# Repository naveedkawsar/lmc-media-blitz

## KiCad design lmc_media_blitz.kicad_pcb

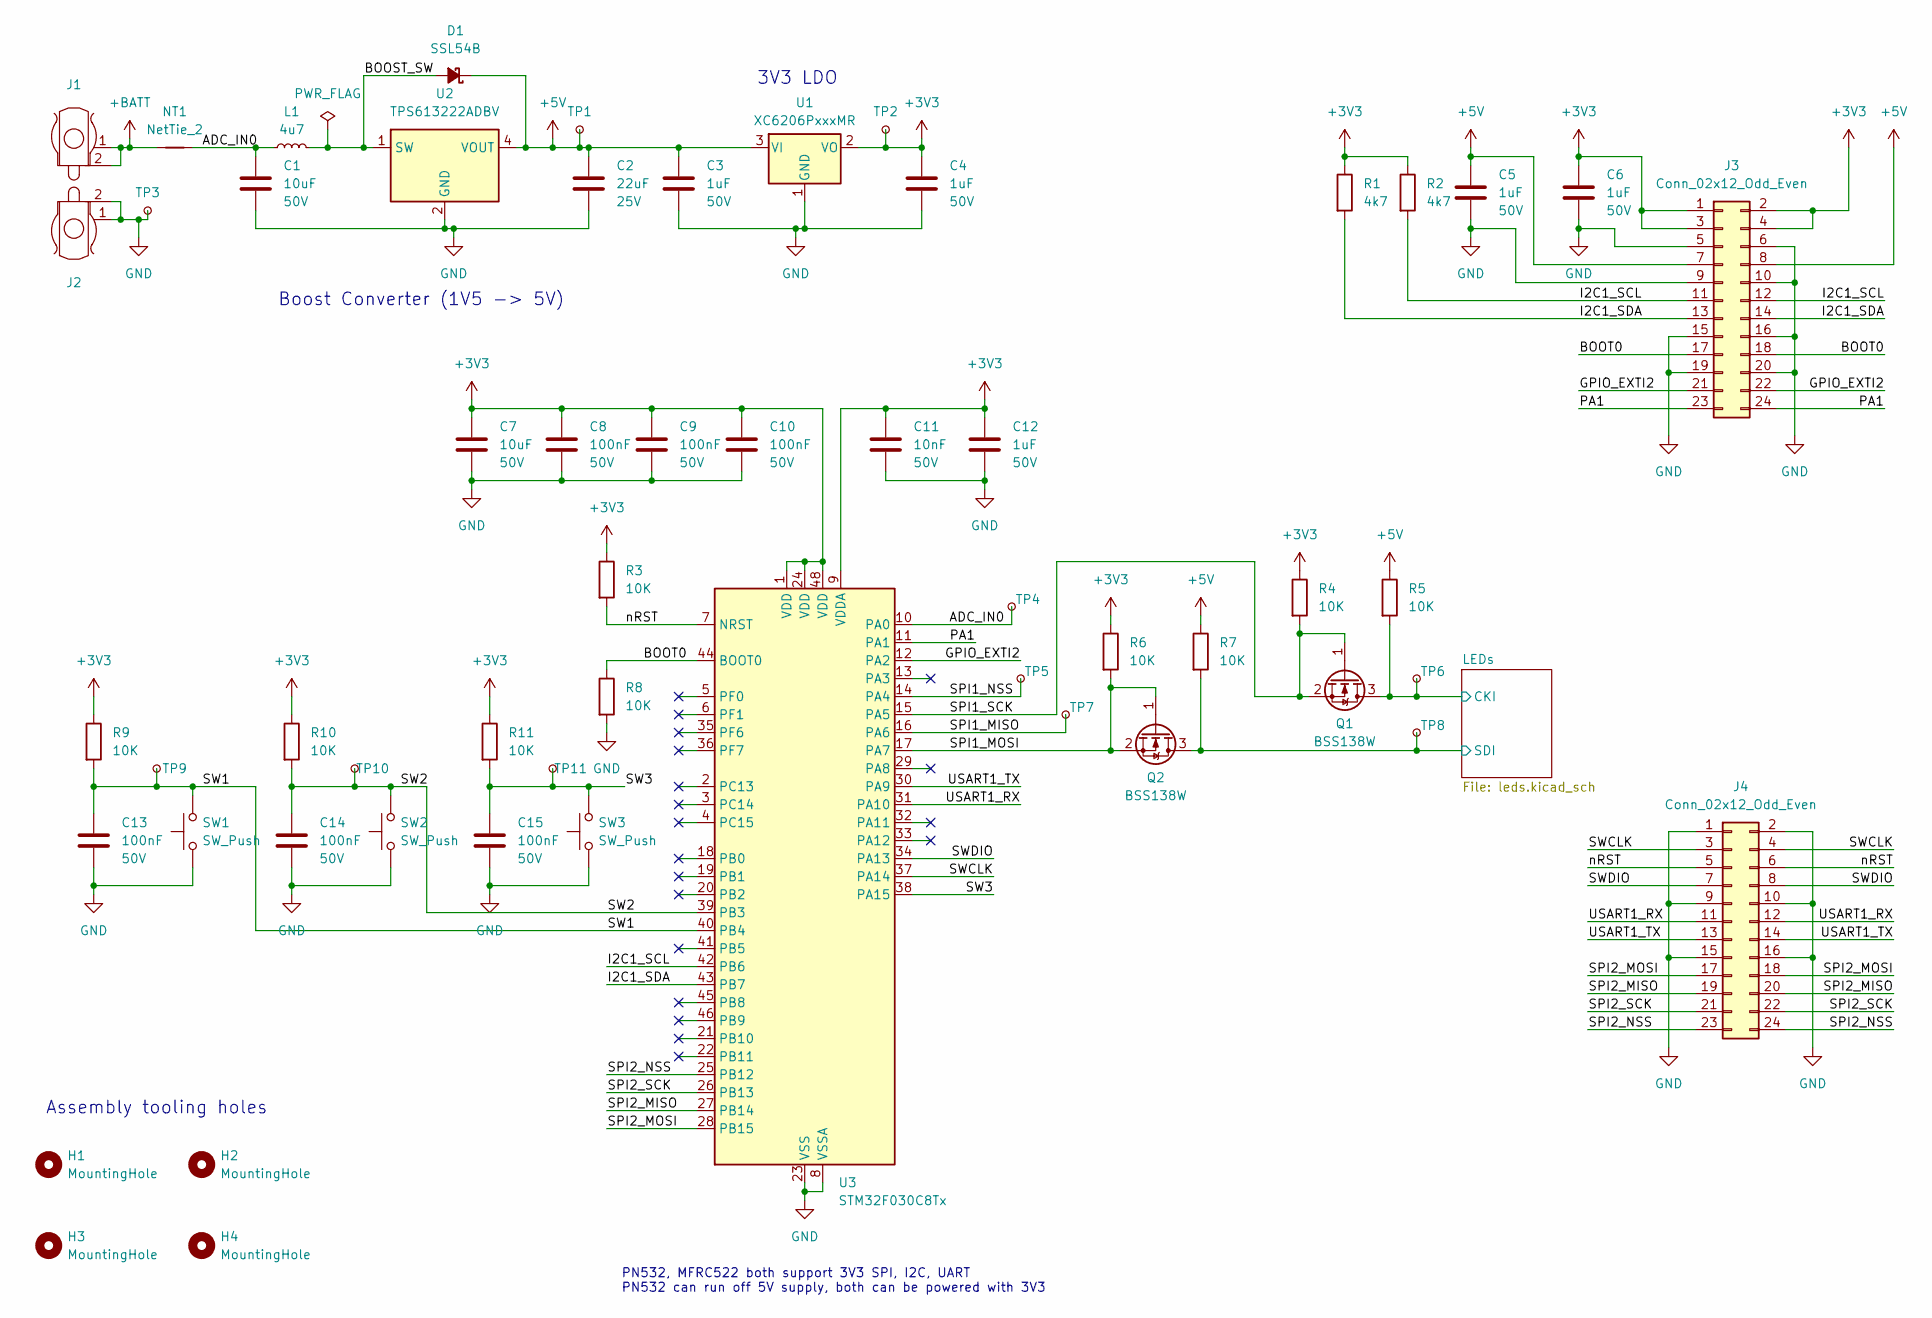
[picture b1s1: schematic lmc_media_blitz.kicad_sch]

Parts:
C1, C7: 10uF; C_0805_2012Metric; Voltage 50V; LCSC Part # C440198
C2: 22uF; C_0805_2012Metric; Voltage 25V; LCSC Part # C16780
C3, C4, C5, C6, C12: 1uF; C_0805_2012Metric; Voltage 50V; LCSC Part # C28323
C8, C9, C10, C13, C14, C15: 100nF; C_0603_1608Metric; Voltage 50V; LCSC Part # C14663
C11: 10nF; C_0603_1608Metric; Voltage 50V; LCSC Part # C57112
D1: SSL54B; D_SMB; LCSC Part # C28646278
H1, H2, H3, H4: MountingHole; JLCPCB_ToolingHole_45.4mils
J1, J2: Keystone82; LCSC Part # C964880
J3, J4: Conn_02x12_Odd_Even; PinHeader_2x12_P2.54mm_Vertical
L1: 4u7; L_Changjiang_FNR4030S; LCSC Part # C167874
NT1: NetTie_2; NetTie-2_SMD_Pad0.5mm
Q1, Q2: BSS138W; SOT-23W; LCSC Part # C28646265
R1, R2: 4k7; R_0805_2012Metric; LCSC Part # C17673
R3, R4, R5, R6, R7, R8, R9, R10, R11: 10K; R_0805_2012Metric; LCSC Part # C17414
SW1, SW2, SW3: SW_Push; SW_Push_1P1T_XKB_TS-1187A; LCSC Part # C318884
TP1, TP2, TP3, TP4, TP5, TP6, TP7, TP8, TP9, TP10, TP11: TestPoint_Small; TestPoint_Pad_D1.5mm
U1: XC6206PxxxMR; SOT-23-3; LCSC Part # C5446
U2: TPS613222ADBV; SOT-23-5; LCSC Part # C2071163
U3: STM32F030C8Tx; LQFP-48_7x7mm_P0.5mm

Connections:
+3V3: C4.1, C6.1, C7.2, C8.1, C9.1, C10.1, C11.1, C12.1, J3.1, J3.2, J3.3, J3.4, R1.1, R2.1, R3.1, R4.1, R6.1, R9.1, R10.1, R11.1, TP2.1, U1.2 (VO), U3.1 (VDD), U3.9 (VDDA), U3.24 (VDD), U3.48 (VDD)
+5V: C2.2, C3.1, C5.1, D1.1 (K), J3.7, J3.8, R5.1, R7.1, TP1.1, U1.3 (VI), U2.4 (VOUT); also elsewhere on the board
+BATT: J1.1, J1.2, NT1.1
/ADC_IN0: C1.2, L1.1, NT1.2, TP4.1, U3.10 (PA0)
/BOOST_SW: D1.2 (A), L1.2, U2.1 (SW)
/BOOT0: J3.17, J3.18, R8.1, U3.44 (BOOT0)
/GPIO_EXTI2: J3.21, J3.22, U3.12 (PA2)
/I2C1_SCL: J3.11, J3.12, R2.2, U3.42 (PB6)
/I2C1_SDA: J3.13, J3.14, R1.2, U3.43 (PB7)
/LEDs/CKI: Q1.3 (D), R5.2, TP6.1; also elsewhere on the board
/LEDs/SDI: Q2.3 (D), R7.2, TP8.1; also elsewhere on the board
/PA1: J3.23, J3.24, U3.11 (PA1)
/SPI1_MISO: TP7.1, U3.16 (PA6)
/SPI1_MOSI: Q2.1 (G), Q2.2 (S), R6.2, U3.17 (PA7)
/SPI1_NSS: TP5.1, U3.14 (PA4)
/SPI1_SCK: Q1.1 (G), Q1.2 (S), R4.2, U3.15 (PA5)
/SPI2_MISO: J4.19, J4.20, U3.27 (PB14)
/SPI2_MOSI: J4.17, J4.18, U3.28 (PB15)
/SPI2_NSS: J4.23, J4.24, U3.25 (PB12)
/SPI2_SCK: J4.21, J4.22, U3.26 (PB13)
/SW1: C13.1, R9.2, SW1.2, TP9.1, U3.40 (PB4)
/SW2: C14.1, R10.2, SW2.2, TP10.1, U3.39 (PB3)
/SW3: C15.1, R11.2, SW3.2, TP11.1, U3.38 (PA15)
/SWCLK: J4.3, J4.4, U3.37 (PA14)
/SWDIO: J4.7, J4.8, U3.34 (PA13)
/USART1_RX: J4.11, J4.12, U3.31 (PA10)
/USART1_TX: J4.13, J4.14, U3.30 (PA9)
/nRST: J4.5, J4.6, R3.2, U3.7 (NRST)
GND: C1.1, C2.1, C3.2, C4.2, C5.2, C6.2, C7.1, C8.2, C9.2, C10.2, C11.2, C12.2, C13.2, C14.2, C15.2, J2.1, J2.2, J3.5, J3.6, J3.9, J3.10, J3.15, J3.16, J3.19, J3.20, J4.1, J4.2, J4.9, J4.10, J4.15, J4.16, R8.2, SW1.1, SW2.1, SW3.1, TP3.1, U1.1 (GND), U2.2 (GND), U3.8 (VSSA), U3.23 (VSS), U3.47 (VSS); also elsewhere on the board

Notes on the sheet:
Boost Converter (1V5 -> 5V)
Assembly tooling holes
3V3 LDO
PN532, MFRC522 both support 3V3 SPI, I2C, UART PN532 can run off 5V supply, both can be powered with 3V3

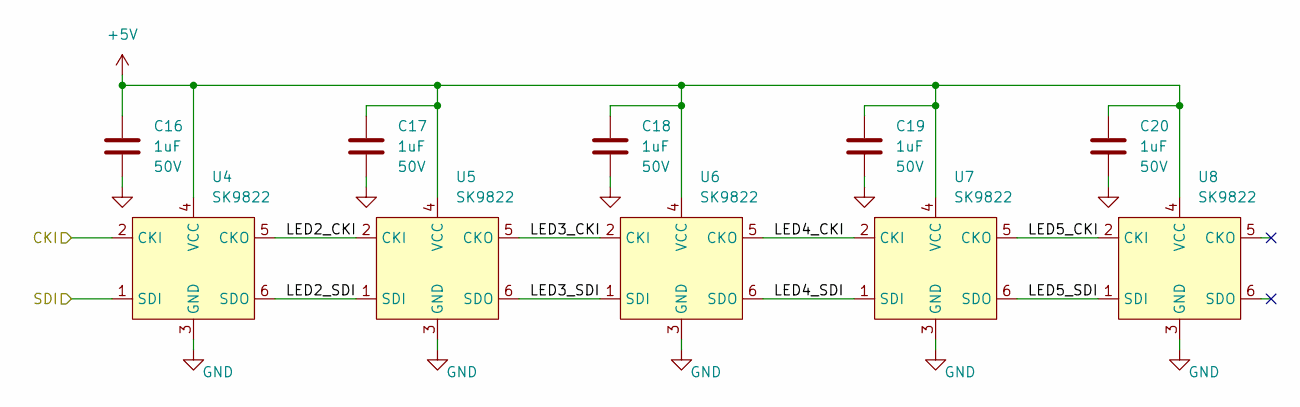
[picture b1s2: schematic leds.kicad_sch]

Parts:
C16, C17, C18, C19, C20: 1uF; C_0805_2012Metric; Voltage 50V; LCSC Part # C28323
U4, U5, U6, U7, U8: SK9822; OPSCO_SK9822; LCSC Part # C5378730

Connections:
+5V: C16.1, C17.1, C18.1, C19.1, C20.1, U4.4 (VCC), U5.4 (VCC), U6.4 (VCC), U7.4 (VCC), U8.4 (VCC); also elsewhere on the board
/LEDs/CKI: U4.2 (CKI); also elsewhere on the board
/LEDs/LED2_CKI: U4.5 (CKO), U5.2 (CKI)
/LEDs/LED2_SDI: U4.6 (SDO), U5.1 (SDI)
/LEDs/LED3_CKI: U5.5 (CKO), U6.2 (CKI)
/LEDs/LED3_SDI: U5.6 (SDO), U6.1 (SDI)
/LEDs/LED4_CKI: U6.5 (CKO), U7.2 (CKI)
/LEDs/LED4_SDI: U6.6 (SDO), U7.1 (SDI)
/LEDs/LED5_CKI: U7.5 (CKO), U8.2 (CKI)
/LEDs/LED5_SDI: U7.6 (SDO), U8.1 (SDI)
/LEDs/SDI: U4.1 (SDI); also elsewhere on the board
GND: C16.2, C17.2, C18.2, C19.2, C20.2, U4.3 (GND), U5.3 (GND), U6.3 (GND), U7.3 (GND), U8.3 (GND); also elsewhere on the board

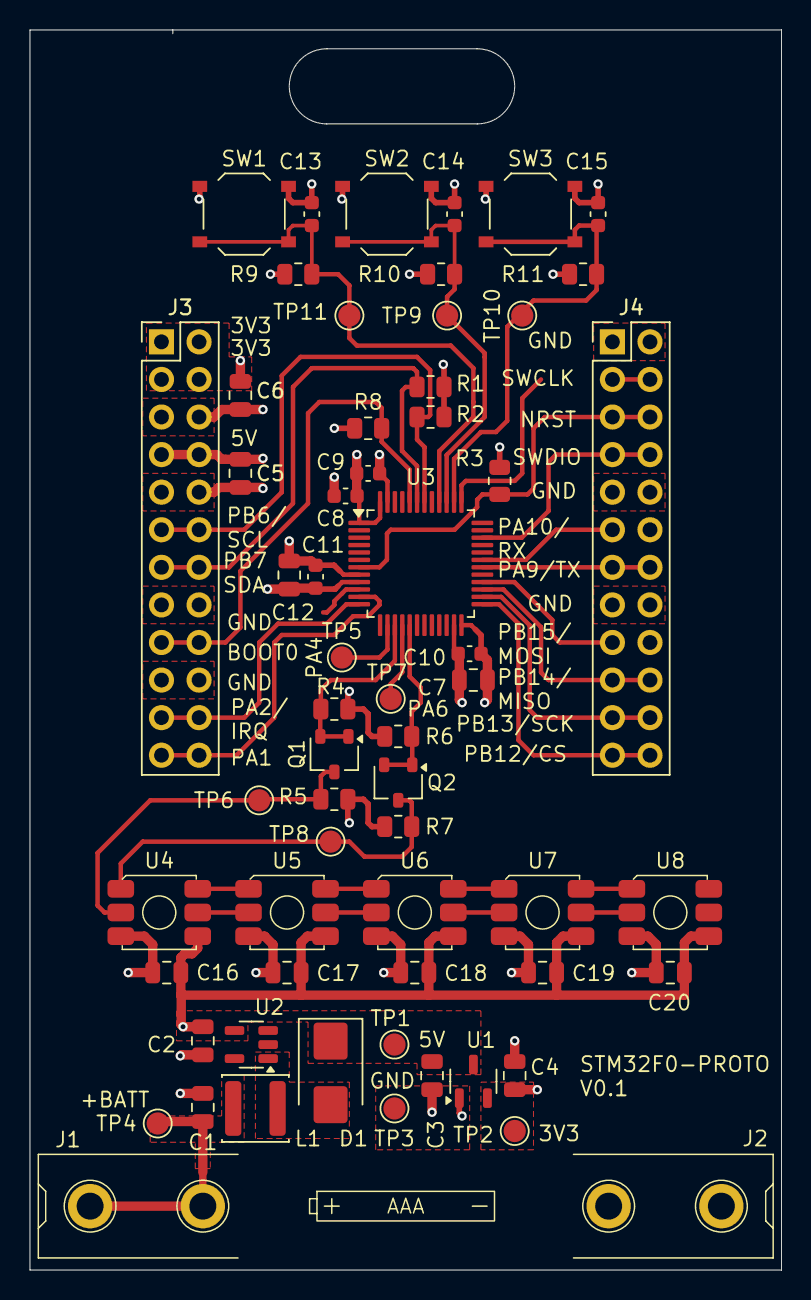
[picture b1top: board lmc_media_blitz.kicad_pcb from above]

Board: 2 copper layers, 50.8 x 83.8 mm, 66 parts (0 on the bottom side), 37 nets.

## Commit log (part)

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2025-05-09 Replaced n-channel FETs, LDO, and SWD connector with Basic JLCPCB parts
2025-05-23 Replaced NFC reader IC with one available from JLCPCB. Added matching circuit components from JLC Basic Parts library. Modified syntax of antenna 3D model to fix loading issue
2025-05-23 Added net labels for readability during layout
2025-05-23 Replaced LPC TSSOP package MCU with QFN package due to unavailability. Added separate decoupling for analog VDD rail. Added tooling holes to board for assembly
2025-05-23 Generated Gerbers and drill files for fabrication
2025-05-24 Minor cleanup. Moved vias to let GND pours flow between islands
2025-05-24 Slight PCB rework
